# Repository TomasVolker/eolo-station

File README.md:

# eolo-station
Estación Meteorológica basa en la EDU-CIAA

Trabajo Práctico Final del Seminario de Sistemas Embebidos de la Facultad de Ingeniería de la Universidad de Buenos Aires

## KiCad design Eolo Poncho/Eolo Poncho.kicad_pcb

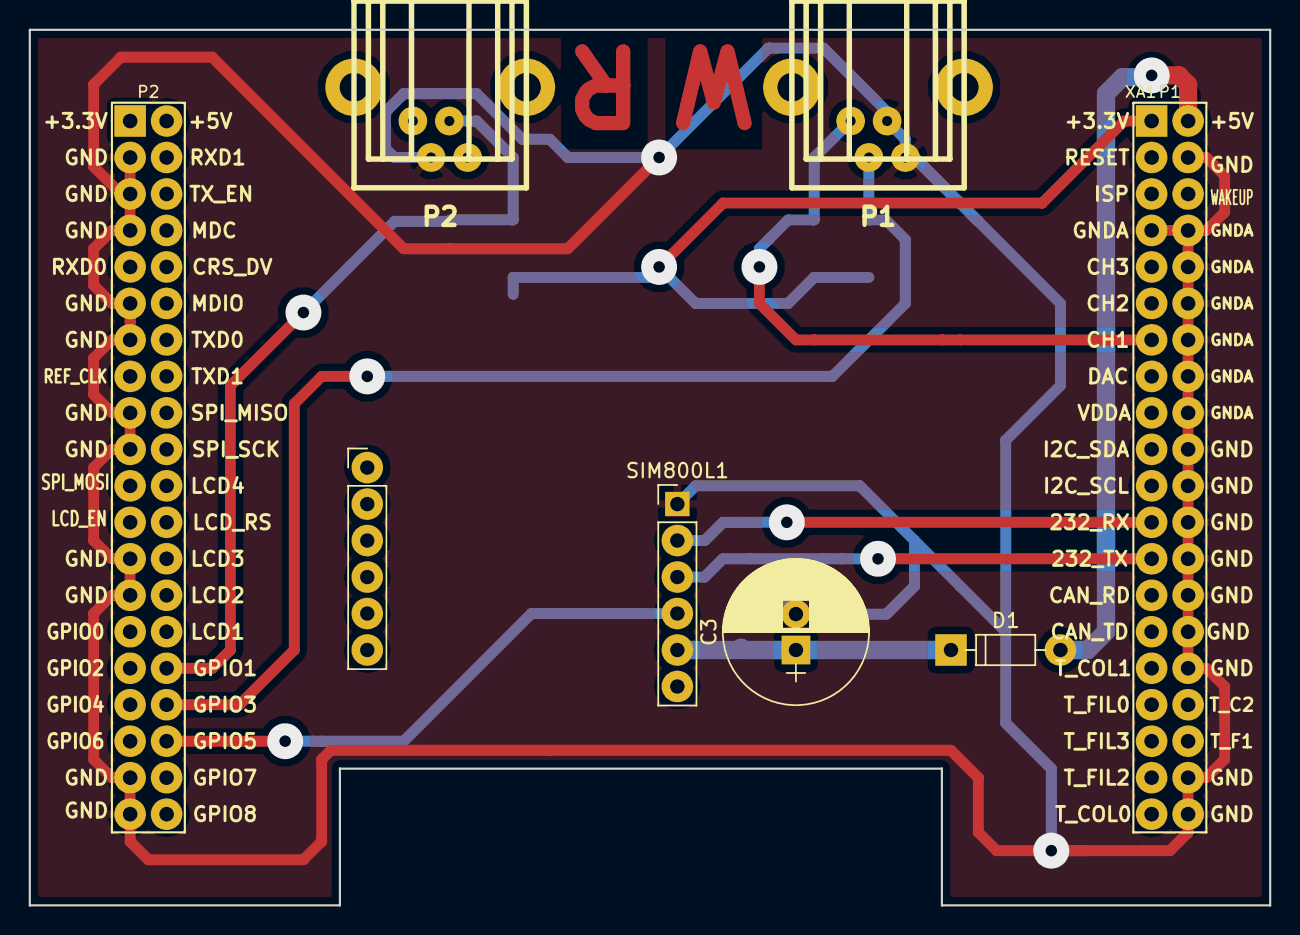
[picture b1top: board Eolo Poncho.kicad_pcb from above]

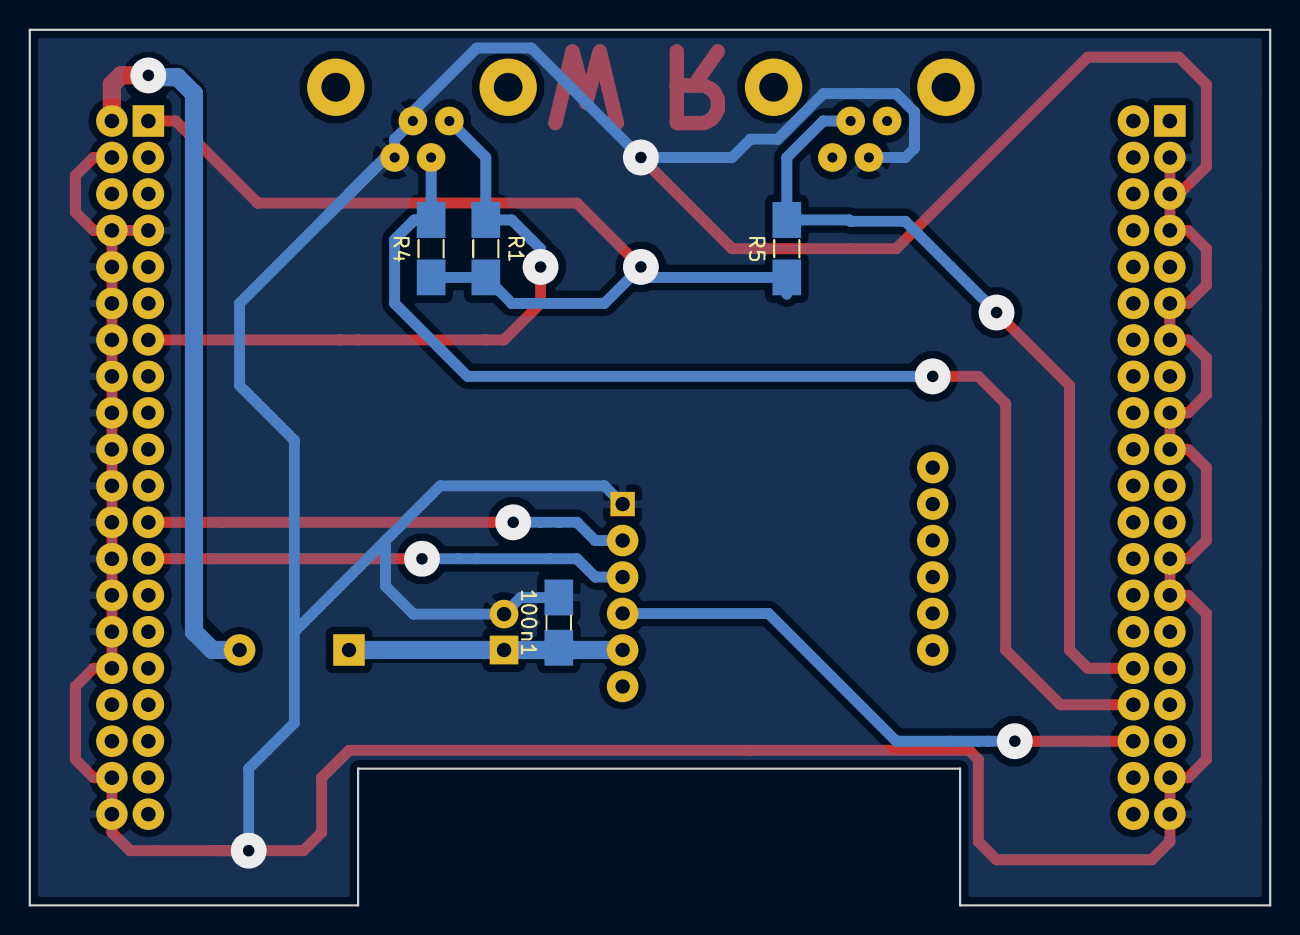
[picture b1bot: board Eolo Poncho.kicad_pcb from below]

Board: 2 copper layers, 86.4 x 61.0 mm, 10 parts (4 on the bottom side), 10 nets.

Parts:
100n1: C; C_0805_HandSoldering
C3: 1000u; CP_Radial_D10.0mm_P2.50mm_hand
D1: 1N4002; D_DO-35_SOD27_P7.62mm_Horizontal
P1: CONN_WIND; RJ11_Female
P2: CONN_RAIN; RJ11_Female
R1, R4, R5: 10k; R_0805_HandSoldering
SIM800L1: SIM800L; Sim800l_module
XA1: Conn_PonchoMP_2x_20x2; Conn_Poncho_Chico

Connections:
+3.3V: R1.2, R4.1, R5.1, XA1.1
+5V: D1.2, XA1.2
/RST: SIM800L1.4, XA1.76
/RXD: SIM800L1.3, XA1.25
/TXD: SIM800L1.2, XA1.23
/VCC: 100n1.1, C3.1, D1.1, SIM800L1.5
/rain_pulse: P2.2, R5.2, XA1.72
/wind_dir_analog: P1.4, R1.1, XA1.13
/wind_speed_pulse: P1.3, R4.2, XA1.74
GND: 100n1.2, C3.2, P1.1, P1.2, P2.3, SIM800L1.1, XA1.4, XA1.7, XA1.8, XA1.10, XA1.12, XA1.14, XA1.16, XA1.18, XA1.20, XA1.22, XA1.24, XA1.26, XA1.28, XA1.30, XA1.32, XA1.38, XA1.40, XA1.43, XA1.45, XA1.47, XA1.51, XA1.53, XA1.57, XA1.59, XA1.65, XA1.67, XA1.77, XA1.79
